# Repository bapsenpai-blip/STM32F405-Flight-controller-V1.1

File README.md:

# STM32F405-Flight-controller-V1.1
After the freaking horrible v1, I have changed a lot to improve my FC as much as possible.

### Changes from the V1
- Remove the SD card slot (took too much space). Using a blackbox instead.
- Remove 1 USB-C connector for ESP32. Now using an usb-mux + slide switch to choose which MCU is connected.
- Cleaner layout, board size changed from freaking big to 50x50mm (30.5x30.5 mounting hole).

### Components
- STM32F405RGT6: doing the basic things of an FC (calculate angles, PID, motor mixer,...)
- ESP32 S3 - WROOM 02: using DroneBrigde method for affordable Telemetry (I have no money to buy an $60 MAVLink Telemetry module)
- 8MHz Crystals from China: 10pF CLoad
- IMU: ICM-20602
- Barometer: BMP280
- Flash Memory: W25Q128JVS (16MB SPI Flash for Blackbox logging)
- USB-C Receptable 2.0 16 pins
- FSUSB42MUX: combining with a slideswitch to change the USB signal to desired MCU.
- Power supply: I'm gonna use an external Buck Converter, because I have no idea about power electronics
- USBLC6-2SC6: ESD protection for USB-C
- 2 AP2112K-3.3Vs: one for STM32 and other main components, one for only ESP32 (ESP32 consumes a lot of current when using Wi-fi/BLE)
- 2 SS14 Diodes: preventing reverse currents
- Resistors and capacitors: based on the recommendation of components' datasheets.

### Pin Mapping & Peripheral Connections

| Peripheral / Interface | Signal Name | MCU Pin | Description / Target |
| :--- | :--- | :--- | :--- |
| **IMU (ICM-20602)** | SPI2_NSS / SCK / MISO / MOSI | `PB12` / `PB13` / `PB14` / `PB15` | SPI Sensor Bus |
| | IMU_DDRY | `PC6` | EXTI Data Ready Interrupt |
| **Blackbox (W25Q128)** | SPI1_NSS / SCK / MISO / MOSI | `PA4` / `PA5` / `PA6` / `PA7` | 16MB SPI NOR Flash |
| **Barometer (BMP280)** | I2C1_SCL / I2C1_SDA | `PB8` / `PB9` | Internal Baro (4.7kΩ pull-ups) |
| **Motors (DSHOT)** | DSHOT_CH1 / CH2 | `PB4` / `PB5` | TIM3_CH1, TIM3_CH2 (to J3 ESC) |
| | DSHOT_CH3 / CH4 | `PB6` / `PB7` | TIM4_CH1, TIM4_CH4 (to J3 ESC) |
| **Telemetry (ESP32-S3)** | UART3_TX / UART3_RX | `PB10` / `PB11` | DroneBridge Telemetry link |
| **RC Receiver (J4)** | UART1_TX / UART1_RX | `PA9` / `PA10` | Serial RX (CRSF / SBUS / IBUS) |
| **GPS / Ext Sensor (J5)** | UART2_TX / UART2_RX | `PA2` / `PA3` | External GPS Serial Port |
| | I2C1_SCL / I2C1_SDA | `PB8` / `PB9` | External Compass / Sensor Bus |
| **ESC Telemetry (J3)** | UART4_RX | `PA1` | ESC Telemetry feedback |
| **Current / Voltage Sensing**| ADC1_IN14 (CURR) | `PC4` | Current sensor via 1kΩ / 100nF filter |
| | ADC1_IN15 (VBAT) | `PC5` | Battery voltage via 10:1 divider (11x) |
| **Status LEDs** | STAT_LED1 / LED2 / LED3 | `PC14` / `PB3` / `PC13` | Debug & status indicators |
| **USB & Debug (J7)** | S_D- / S_D+ | `PA11` / `PA12` | USB FS (via FSUSB42 MUX) |
| | SWDIO / SWCLK | `PA13` / `PA14` | SWD Debug port |

### Status & Firmware
- [x] Hardware verification: Validated on a custom STM32F405 breakout board (SPI, I2C, UART peripherals verified and working stably).
- [x] V1.1 PCB design & layout completed (ready for manufacturing/bring-up).
- [ ] Bring-up V1.1 integrated board (test power rails, USB mux swiSching, and onboard sensors).
- [ ] Port and configure open-source flight firmware (Betaflight / INAV / ArduPilot target).
- [ ] Bring-up ESP32-CS DroneBridge telemetry link.
- [ ] Bench test with 4-in-1 ESC (DShot) & maiden flight test.

**Firmware & Tools:** 
- Open-source flight controller firmware (target bring-up)
- ESP-IDF / DroneBridge for ESP32-S3
- VS Code - PlatformIO for low-level validation & debugging

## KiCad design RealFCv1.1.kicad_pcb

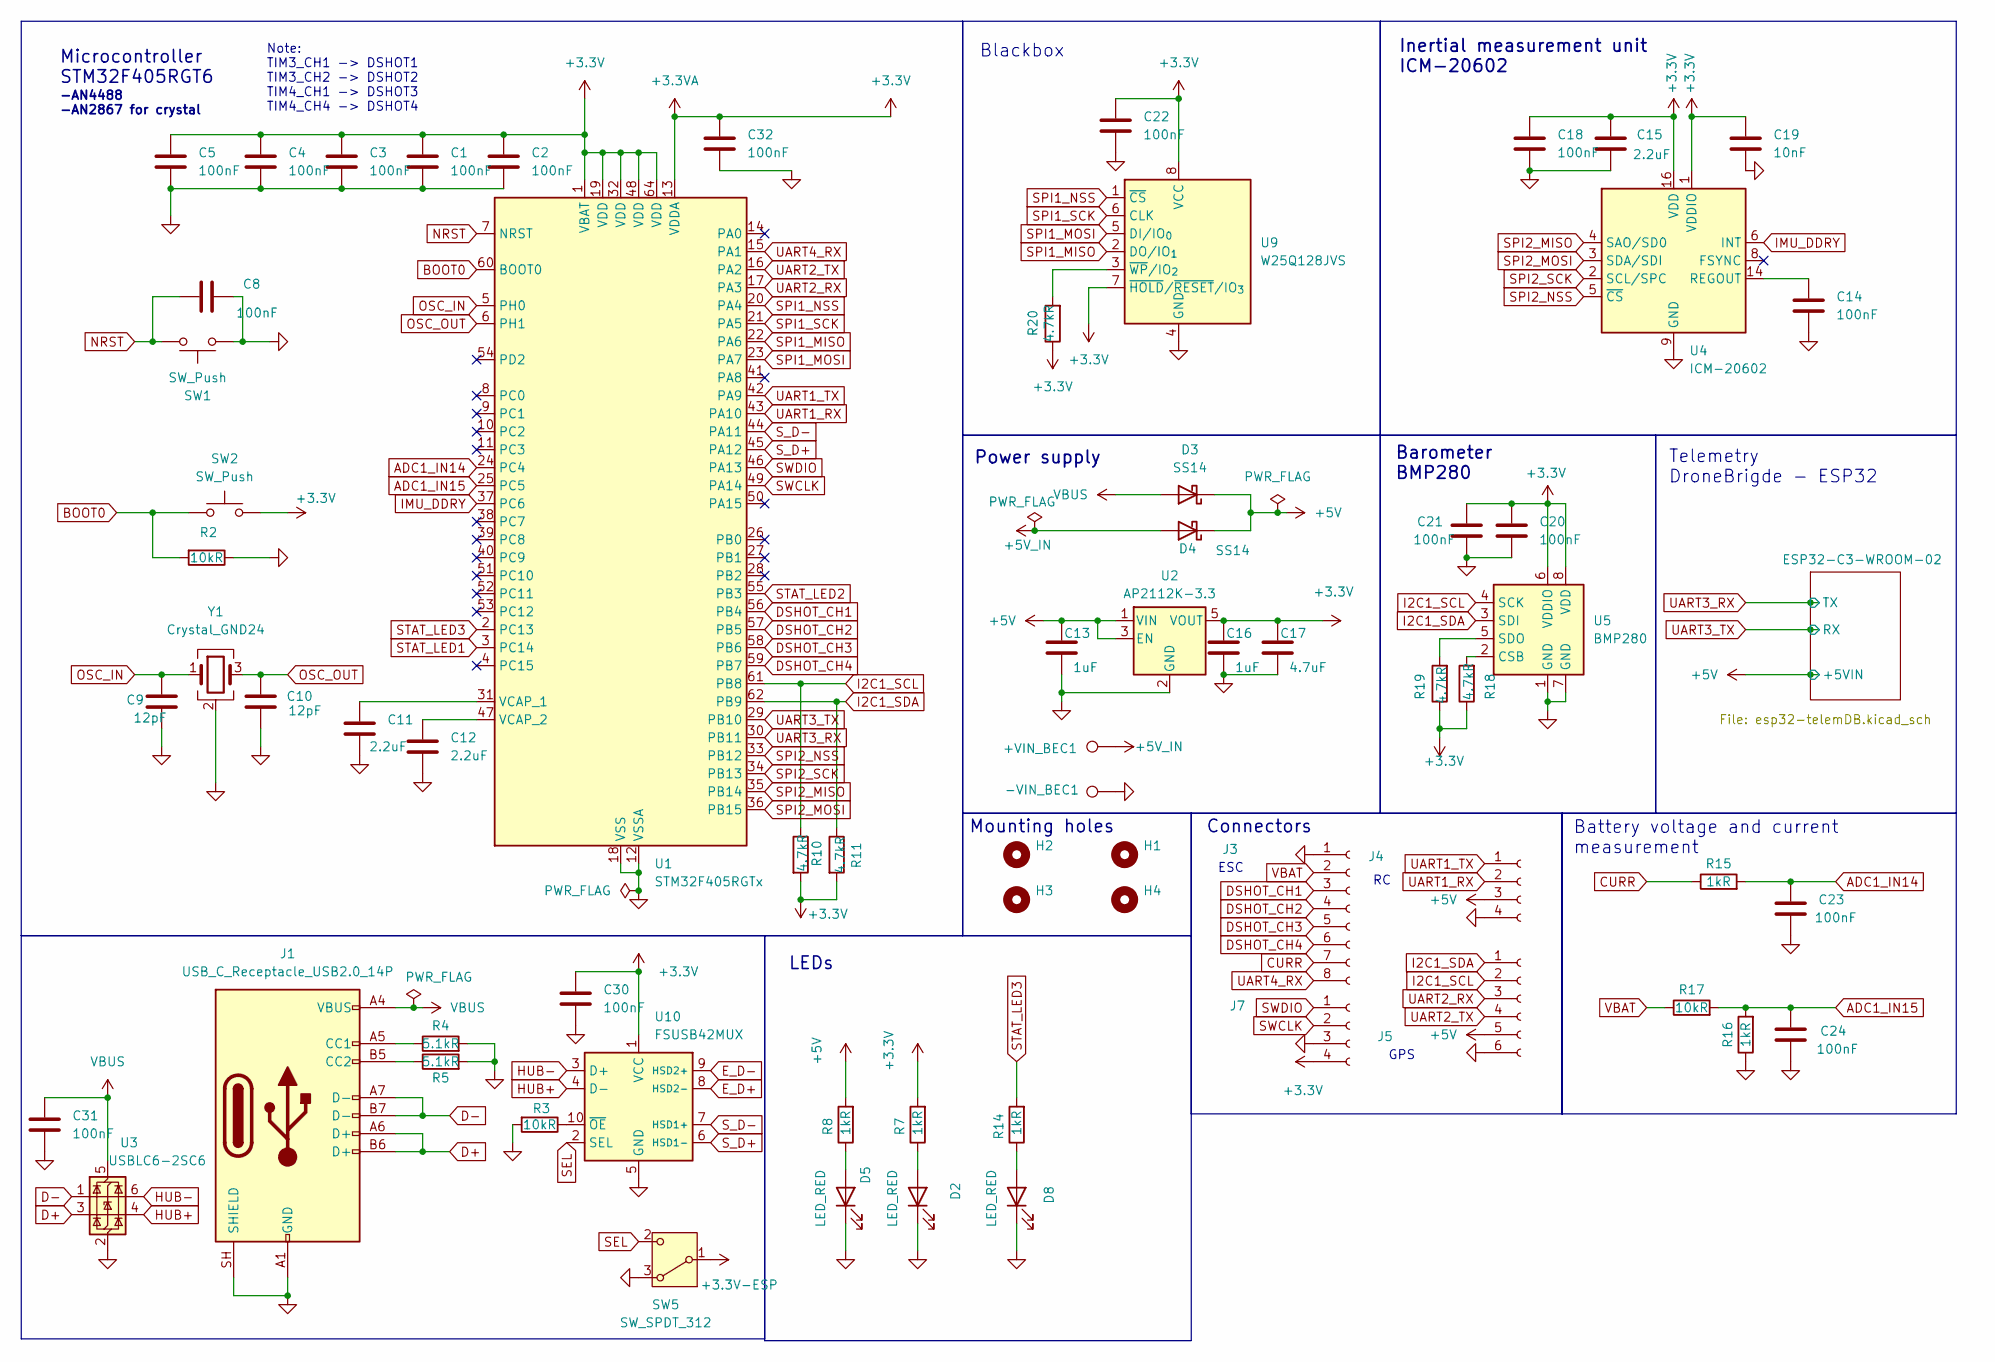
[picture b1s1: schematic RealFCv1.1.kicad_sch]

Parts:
+VIN_BEC1: TestPoint; TestPoint_THTPad_3.0x3.0mm_Drill1.5mm
-VIN_BEC1: TestPoint; TestPoint_THTPad_3.0x3.0mm_Drill1.5mm
C1, C2, C3, C4, C5, C8, C14, C18, C20, C21, C22, C23, C24, C30, C31, C32: 100nF; C_0402_1005Metric_Pad0.74x0.62mm_HandSolder
C9, C10: 12pF; C_0402_1005Metric_Pad0.74x0.62mm_HandSolder
C11, C12, C15: 2.2uF; C_0402_1005Metric_Pad0.74x0.62mm_HandSolder
C13, C16: 1uF; C_0402_1005Metric_Pad0.74x0.62mm_HandSolder
C17: 4.7uF; C_0805_2012Metric_Pad1.18x1.45mm_HandSolder
C19: 10nF; C_0402_1005Metric_Pad0.74x0.62mm_HandSolder
D2, D5, D8: LED_RED; LED_0402_1005Metric_Pad0.77x0.64mm_HandSolder
D3, D4: SS14; D_SMA
H1, H2, H3, H4: MountingHole; MountingHole_3.2mm_M3
J1: USB_C_Receptacle_USB2.0_14P; USB_C_Receptacle_HRO_TYPE-C-31-M-12
J3: Conn_01x08_Socket; JST_SH_SM08B-SRSS-TB_1x08-1MP_P1.00mm_Horizontal
J4: Conn_01x04_Socket; JST_SH_SM04B-SRSS-TB_1x04-1MP_P1.00mm_Horizontal
J5: Conn_01x06_Socket; JST_SH_SM06B-SRSS-TB_1x06-1MP_P1.00mm_Horizontal
J7: Conn_01x04_Socket; PinHeader_1x04_P2.54mm_Vertical
R2, R3, R17: 10kR; R_0402_1005Metric_Pad0.72x0.64mm_HandSolder
R4, R5: 5.1kR; R_0402_1005Metric_Pad0.72x0.64mm_HandSolder
R7, R8, R14, R15, R16: 1kR; R_0402_1005Metric_Pad0.72x0.64mm_HandSolder
R10, R11, R18, R19, R20: 4.7kR; R_0402_1005Metric_Pad0.72x0.64mm_HandSolder
SW1, SW2: SW_Push; SW_Push_1P1T-SH_NO_CK_KMR2xxG
SW5: SW_SPDT_312; SW_SPDT_PCM12
U1: STM32F405RGTx; LQFP-64_10x10mm_P0.5mm
U2: AP2112K-3.3; SOT-23-5_HandSoldering
U3: USBLC6-2SC6; SOT-23-6_Handsoldering
U4: ICM-20602; LGA-16_3x3mm_P0.5mm_LayoutBorder3x5y
U5: BMP280; Bosch_LGA-8_2x2.5mm_P0.65mm_ClockwisePinNumbering
U9: W25Q128JVS; SOIC-8_5.3x5.3mm_P1.27mm
U10: FSUSB42MUX; MSOP-10_3x3mm_P0.5mm
Y1: Crystal_GND24; Crystal_SMD_3225-4Pin_3.2x2.5mm_HandSoldering

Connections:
+3.3V: C1.1, C2.1, C3.1, C4.1, C5.1, C15.1, C16.1, C17.1, C18.1, C19.1, C20.1, C21.1, C22.2, C30.2, C32.1, J7.4, R7.2, R10.2, R11.2, R18.1, R19.1, R20.1, SW2.2, U1.1 (VBAT), U1.13 (VDDA), U1.19 (VDD), U1.32 (VDD), U1.48 (VDD), U1.64 (VDD), U2.5 (VOUT), U4.1 (VDDIO), U4.16 (VDD), U5.6 (VDDIO), U5.8 (VDD), U9.7 (~HOLD/~RESET/IO_{3}), U9.8 (VCC), U10.1 (VCC)
+3.3V-ESP: SW5.1 (B); also elsewhere on the board
+5V: C13.1, D3.1 (K), D4.1 (K), J4.3, J5.5, R8.2, U2.1 (VIN), U2.3 (EN); also elsewhere on the board
+5V_IN: +VIN_BEC1.1 (1_1), D4.2 (A)
ADC1_IN14: C23.1, R15.2, U1.24 (PC4)
ADC1_IN15: C24.1, R16.2, R17.2, U1.25 (PC5)
BOOT0: R2.2, SW2.1, U1.60 (BOOT0)
CURR: J3.7, R15.1
D+: J1.A6 (D+), J1.B6 (D+), U3.3 (I/O2)
D-: J1.A7 (D-), J1.B7 (D-), U3.1 (I/O1)
DSHOT_CH1: J3.3, U1.56 (PB4)
DSHOT_CH2: J3.4, U1.57 (PB5)
DSHOT_CH3: J3.5, U1.58 (PB6)
DSHOT_CH4: J3.6, U1.59 (PB7)
E_D+: U10.8 (HSD2-); also elsewhere on the board
E_D-: U10.9 (HSD2+); also elsewhere on the board
GND: -VIN_BEC1.1 (1_1), C1.2, C2.2, C3.2, C4.2, C5.2, C8.2, C9.2, C10.2, C11.2, C12.2, C13.2, C14.2, C15.2, C16.2, C17.2, C18.2, C19.2, C20.2, C21.2, C22.1, C23.2, C24.2, C30.1, C31.1, C32.2, D2.1 (K), D5.1 (K), D8.1 (K), J1.A1 (GND), J1.A12 (GND), J1.B1 (GND), J1.B12 (GND), J1.SH (SHIELD), J3.1, J4.4, J5.6, J7.3, R2.1, R3.2, R4.2, R5.2, R16.1, SW1.1, SW5.3 (A), U1.12 (VSSA), U1.18 (VSS), U1.63 (VSS), U2.2 (GND), U3.2 (GND), U4.9 (GND), U4.10 (GND), U4.11 (GND), U4.12 (GND), U4.13 (GND), U4.15 (GND), U5.1 (GND), U5.7 (GND), U9.4 (GND), U10.5 (GND), Y1.2 (G), Y1.4 (G); also elsewhere on the board
HUB+: U3.4 (I/O2), U10.4 (D-)
HUB-: U3.6 (I/O1), U10.3 (D+)
I2C1_SCL: J5.2, R10.1, U1.61 (PB8), U5.4 (SCK)
I2C1_SDA: J5.1, R11.1, U1.62 (PB9), U5.3 (SDI)
IMU_DDRY: U1.37 (PC6), U4.6 (INT)
NRST: C8.1, SW1.2, U1.7 (NRST)
unnamed: D2.2 (A), R7.1
unnamed: D5.2 (A), R8.1
unnamed: D8.2 (A), R14.1
unnamed: J1.A5 (CC1), R4.1
unnamed: J1.B5 (CC2), R5.1
unnamed: C11.1, U1.31 (VCAP_1)
unnamed: C12.1, U1.47 (VCAP_2)
unnamed: C14.1, U4.14 (REGOUT)
unnamed: R18.2, U5.2 (CSB)
unnamed: R19.2, U5.5 (SDO)
unnamed: R20.2, U9.3 (~WP/IO_{2})
unnamed: R3.1, U10.10 (~OE)
OSC_IN: C9.1, U1.5 (PH0), Y1.1
OSC_OUT: C10.1, U1.6 (PH1), Y1.3
SEL: SW5.2 (C), U10.2 (SEL)
SPI1_MISO: U1.22 (PA6), U9.2 (DO/IO_{1})
SPI1_MOSI: U1.23 (PA7), U9.5 (DI/IO_{0})
SPI1_NSS: U1.20 (PA4), U9.1 (~CS)
SPI1_SCK: U1.21 (PA5), U9.6 (CLK)
SPI2_MISO: U1.35 (PB14), U4.4 (SAO/SD0)
SPI2_MOSI: U1.36 (PB15), U4.3 (SDA/SDI)
SPI2_NSS: U1.33 (PB12), U4.5 (~CS)
SPI2_SCK: U1.34 (PB13), U4.2 (SCL/SPC)
STAT_LED1: U1.3 (PC14)
STAT_LED2: U1.55 (PB3)
STAT_LED3: R14.2, U1.2 (PC13)
SWCLK: J7.2, U1.49 (PA14)
SWDIO: J7.1, U1.46 (PA13)
S_D+: U1.45 (PA12), U10.6 (HSD1-)
S_D-: U1.44 (PA11), U10.7 (HSD1+)
UART1_RX: J4.2, U1.43 (PA10)
UART1_TX: J4.1, U1.42 (PA9)
UART2_RX: J5.3, U1.17 (PA3)
UART2_TX: J5.4, U1.16 (PA2)
UART3_RX: U1.30 (PB11); also elsewhere on the board
UART3_TX: U1.29 (PB10); also elsewhere on the board
UART4_RX: J3.8, U1.15 (PA1)
VBAT: J3.2, R17.1
VBUS: C31.2, D3.2 (A), J1.A4 (VBUS), J1.A9 (VBUS), J1.B4 (VBUS), J1.B9 (VBUS), U3.5 (VBUS)

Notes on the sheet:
Microcontroller STM32F405RGT6
Note: TIM3_CH1 -> DSHOT1 TIM3_CH2 -> DSHOT2 TIM4_CH1 -> DSHOT3 TIM4_CH4 -> DSHOT4
ESC
Telemetry DroneBrigde - ESP32
Inertial measurement unit ICM-20602
GPS
Barometer BMP280
Power supply
LEDs
Blackbox
Battery voltage and current measurement
Mounting holes
Connectors
-AN4488 -AN2867 for crystal

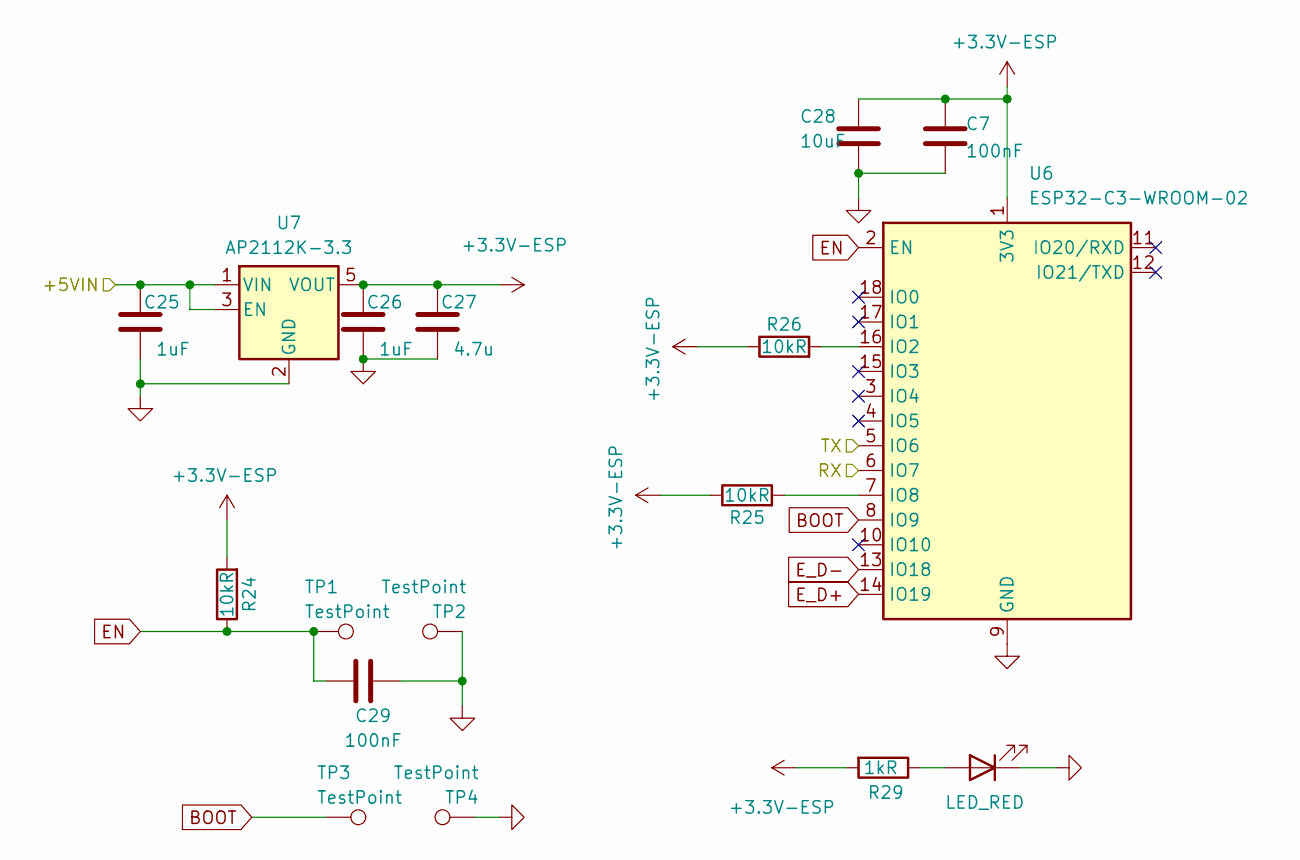
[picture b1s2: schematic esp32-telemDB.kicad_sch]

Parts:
C7, C29: 100nF; C_0402_1005Metric_Pad0.74x0.62mm_HandSolder
C25, C26: 1uF; C_0402_1005Metric_Pad0.74x0.62mm_HandSolder
C27: 4.7u; C_0805_2012Metric_Pad1.18x1.45mm_HandSolder
C28: 10uF; C_0603_1608Metric_Pad1.08x0.95mm_HandSolder
D12: LED_RED; LED_0402_1005Metric_Pad0.77x0.64mm_HandSolder
R24, R25, R26: 10kR; R_0402_1005Metric_Pad0.72x0.64mm_HandSolder
R29: 1kR; R_0402_1005Metric_Pad0.72x0.64mm_HandSolder
TP1, TP2, TP3, TP4: TestPoint; TestPoint_Pad_D1.0mm
U6: ESP32-C3-WROOM-02
U7: AP2112K-3.3; SOT-23-5_HandSoldering

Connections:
+3.3V-ESP: C7.1, C26.1, C27.1, C28.1, R24.2, R25.1, R26.1, R29.2, U6.1 (3V3), U7.5 (VOUT); also elsewhere on the board
+5V: C25.1, U7.1 (VIN), U7.3 (EN); also elsewhere on the board
BOOT: TP3.1 (1_1), U6.8 (IO9)
EN: C29.1, R24.1, TP1.1 (1_1), U6.2 (EN)
E_D+: U6.14 (IO19); also elsewhere on the board
E_D-: U6.13 (IO18); also elsewhere on the board
GND: C7.2, C25.2, C26.2, C27.2, C28.2, C29.2, D12.1 (K), TP2.1 (1_1), TP4.1 (1_1), U6.9 (GND), U6.19 (GND), U7.2 (GND); also elsewhere on the board
unnamed: D12.2 (A), R29.1
unnamed: R26.2, U6.16 (IO2)
unnamed: R25.2, U6.7 (IO8)
UART3_RX: U6.5 (IO6); also elsewhere on the board
UART3_TX: U6.6 (IO7); also elsewhere on the board

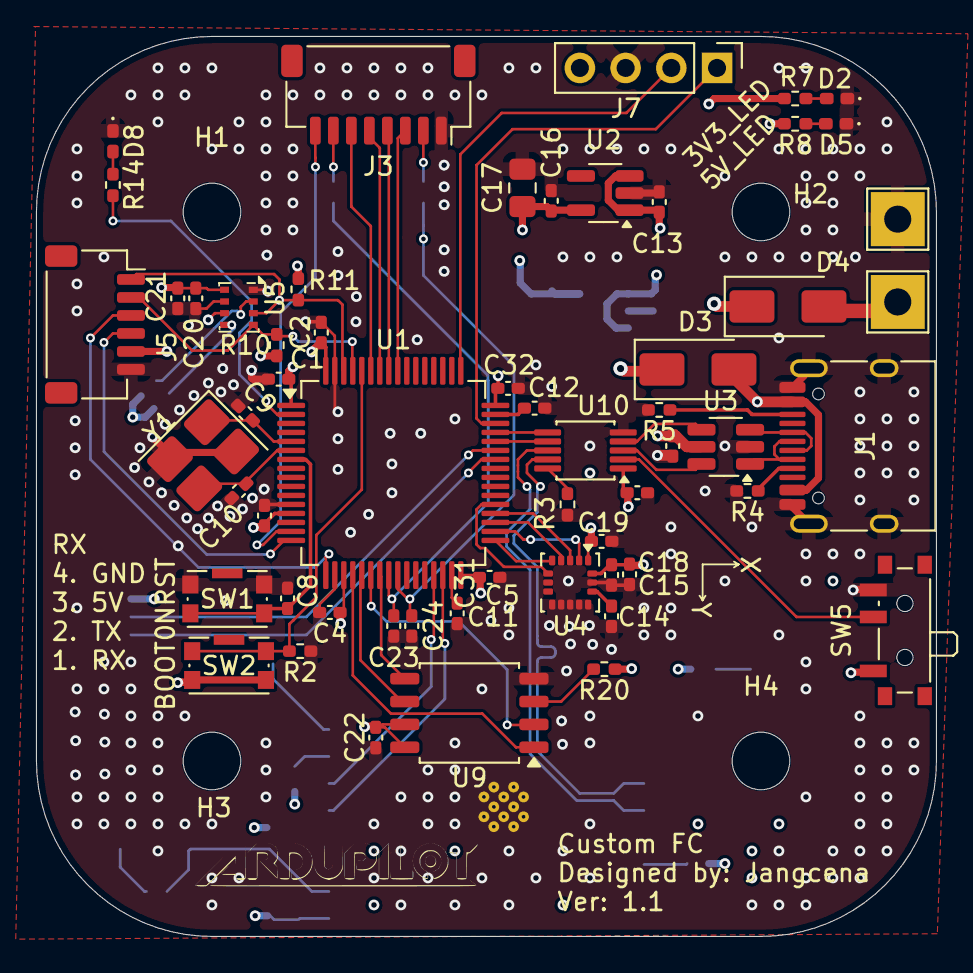
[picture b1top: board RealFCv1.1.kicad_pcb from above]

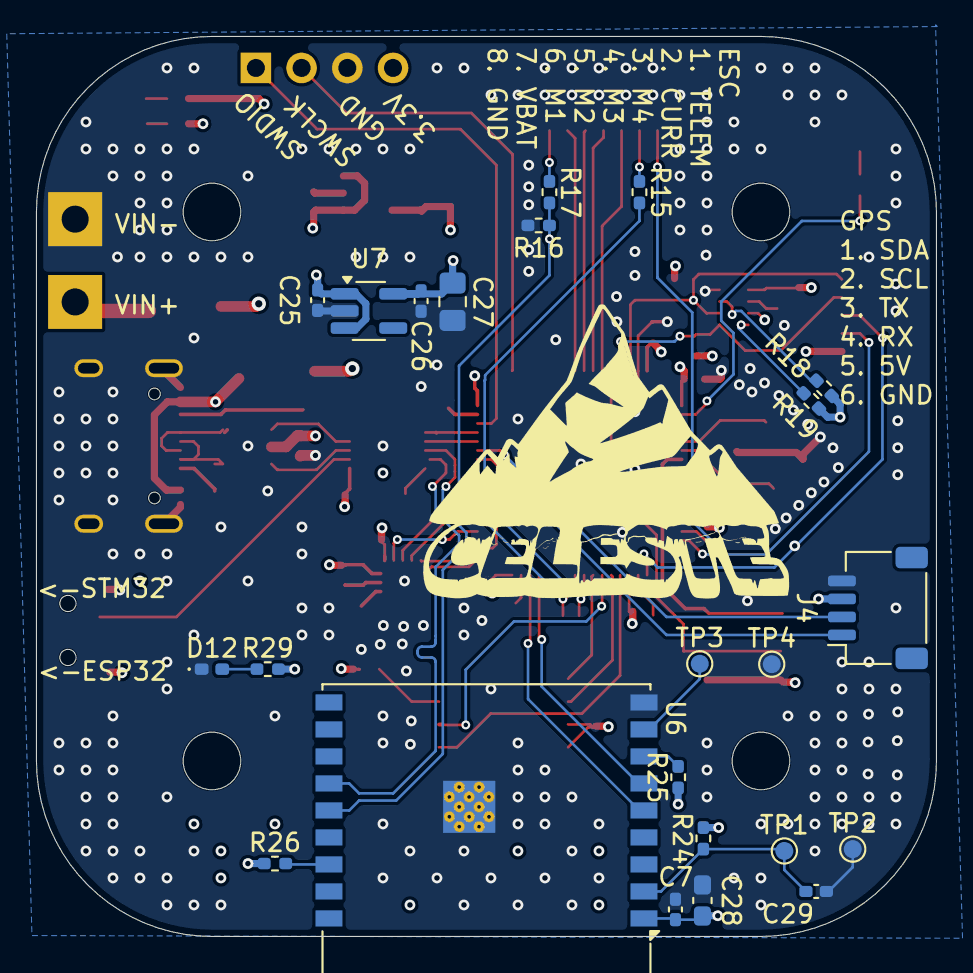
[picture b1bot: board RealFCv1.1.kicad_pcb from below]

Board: 4 copper layers, 50.0 x 50.0 mm, 84 parts (23 on the bottom side), 65 nets.
